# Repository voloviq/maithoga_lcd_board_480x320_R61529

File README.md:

# maithoga_lcd_board_480x320_R61529
PCB Board for Maithoga display with resolution 480x320 based on chip R61529 compatible with ILI9481.

Access to display signal is possible with goldpin described below and fpc compatible with LicheePi Zero board.

Display view

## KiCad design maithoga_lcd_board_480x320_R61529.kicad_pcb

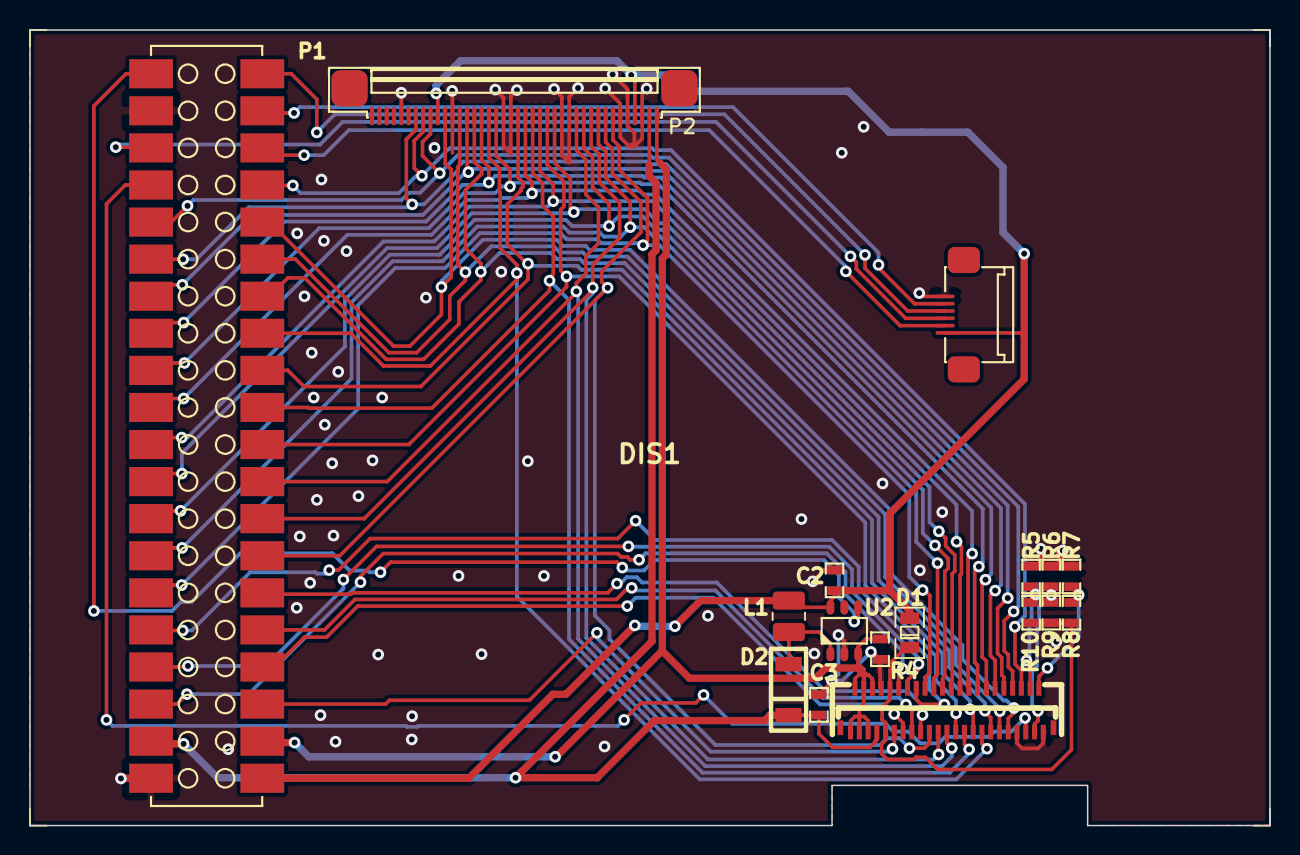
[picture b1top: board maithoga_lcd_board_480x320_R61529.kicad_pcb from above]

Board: 2 copper layers, 85.0 x 54.5 mm, 16 parts (0 on the bottom side), 44 nets.

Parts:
C2: 10uF/10V; 10uF_10V_0603
C3: 1uF_0603
D1: BAS386; BAS386_MICROMELF
D2: MBR0520L; MBR0520L_SOD123
DIS1: maithoga_tft_480x320_rgb_with_capacitive_ts
L1: 22uH; 22uH_2520
P1: Display Connector; Goldpin_20_2_2_54mm_SMT
P2: LicheePi_Con; 40pin_fpc_top_0_5mm
R4: 10R; 10R_0603
R5, R6, R8: 0R_NA; 0R_0603
R7, R9, R10: 0R; 0R_0603
U2: DIO5661ST6

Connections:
3V3: C2.2, D1.1, DIS1.P1, L1.1, P1.1, P2.10, P2.37, U2.6
/Display and Touchscreen/BACKLIGHT_PWM: P1.40, U2.4
/Display and Touchscreen/DISP_D0: DIS1.18, P1.12, P2.34
/Display and Touchscreen/DISP_D1: DIS1.19, P1.13, P2.33
/Display and Touchscreen/DISP_D2: DIS1.20, P1.14, P2.32
/Display and Touchscreen/DISP_D3: DIS1.21, P1.15, P2.31
/Display and Touchscreen/DISP_D4: DIS1.22, P1.16, P2.30
/Display and Touchscreen/DISP_D5: DIS1.23, P1.17, P2.29
/Display and Touchscreen/DISP_D6: DIS1.24, P1.18, P2.26
/Display and Touchscreen/DISP_D7: DIS1.25, P1.19, P2.25
/Display and Touchscreen/DISP_D8: DIS1.26, P1.20, P2.24
/Display and Touchscreen/DISP_D9: DIS1.27, P1.21, P2.23
/Display and Touchscreen/DISP_D10: DIS1.28, P1.22, P2.22
/Display and Touchscreen/DISP_D11: DIS1.29, P1.23, P2.21
/Display and Touchscreen/DISP_D12: DIS1.30, P1.24, P2.18
/Display and Touchscreen/DISP_D13: DIS1.31, P1.25, P2.17
/Display and Touchscreen/DISP_D14: DIS1.32, P1.26, P2.16
/Display and Touchscreen/DISP_D15: DIS1.33, P1.27, P2.15
/Display and Touchscreen/DISP_D16: DIS1.34, P1.28, P2.14
/Display and Touchscreen/DISP_D17: DIS1.35, P1.29, P2.13
/Display and Touchscreen/DISP_DOTCLK: DIS1.37, P1.31, P2.11
/Display and Touchscreen/DISP_ENABLE: DIS1.36, P1.30, P2.7
/Display and Touchscreen/DISP_HSYNC: DIS1.38, P1.32, P2.9
/Display and Touchscreen/DISP_RS: DIS1.13, P1.7
/Display and Touchscreen/DISP_SDA: DIS1.16, P1.10
/Display and Touchscreen/DISP_SDO: DIS1.17, P1.11
/Display and Touchscreen/DISP_TE: DIS1.11, P1.5
/Display and Touchscreen/DISP_VSYNC: DIS1.40, P1.33, P2.8
/Display and Touchscreen/DISP_~CS~: DIS1.12, P1.6
/Display and Touchscreen/DISP_~RD~: DIS1.15, P1.9
/Display and Touchscreen/DISP_~RESET~: DIS1.41, P1.34
/Display and Touchscreen/DISP_~WR~: DIS1.14, P1.8
/Display and Touchscreen/LCD_LED_A: C3.1, D2.1, DIS1.7, P1.4, P2.39
/Display and Touchscreen/LCD_LED_K: DIS1.1, DIS1.2, DIS1.3, DIS1.4, DIS1.5, DIS1.6, P1.3, P2.40, R4.1, U2.3
/Display and Touchscreen/TOUCHSCREEN_INT: DIS1.P4, P1.39
/Display and Touchscreen/TOUCHSCREEN_SCL: DIS1.P3, P1.36
/Display and Touchscreen/TOUCHSCREEN_SDA: DIS1.P2, P1.35
/Standard Goldpin Connector/TOUCHSCREEN_RESET: DIS1.P5, P1.37
GND: C2.1, C3.2, DIS1.8, DIS1.39, DIS1.45, DIS1.P6, P1.2, P1.38, P2.5, P2.12, P2.19, P2.20, P2.27, P2.28, P2.35, P2.36, P2.38, R4.2, R5.2, R6.2, R7.2, U2.2
unnamed: D1.2, DIS1.9, DIS1.10, R8.1, R9.1, R10.1
unnamed: D2.2, L1.2, U2.1
unnamed: DIS1.42, R5.1, R10.2
unnamed: DIS1.43, R6.1, R9.2
unnamed: DIS1.44, R7.1, R8.2

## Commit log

2020-07-08 Added display view
2020-07-08 Schematic in progress
2020-07-08 Filled hierarchical sheets
2020-07-08 Schematic ready, need check
2020-07-08 Schematic finished, pcb tracking started
2020-07-08 Added resistor mode select on schematic
2020-07-09 Added outline on pcb
2020-07-09 Tracking in progress
2020-08-04 Tracking finished
2020-08-04 Generated gerbers
2020-08-13 Added new capacitive display
2020-12-11 Added zip gerber file
